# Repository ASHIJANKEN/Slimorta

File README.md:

# Slimorta
A slim and portable keyboad.

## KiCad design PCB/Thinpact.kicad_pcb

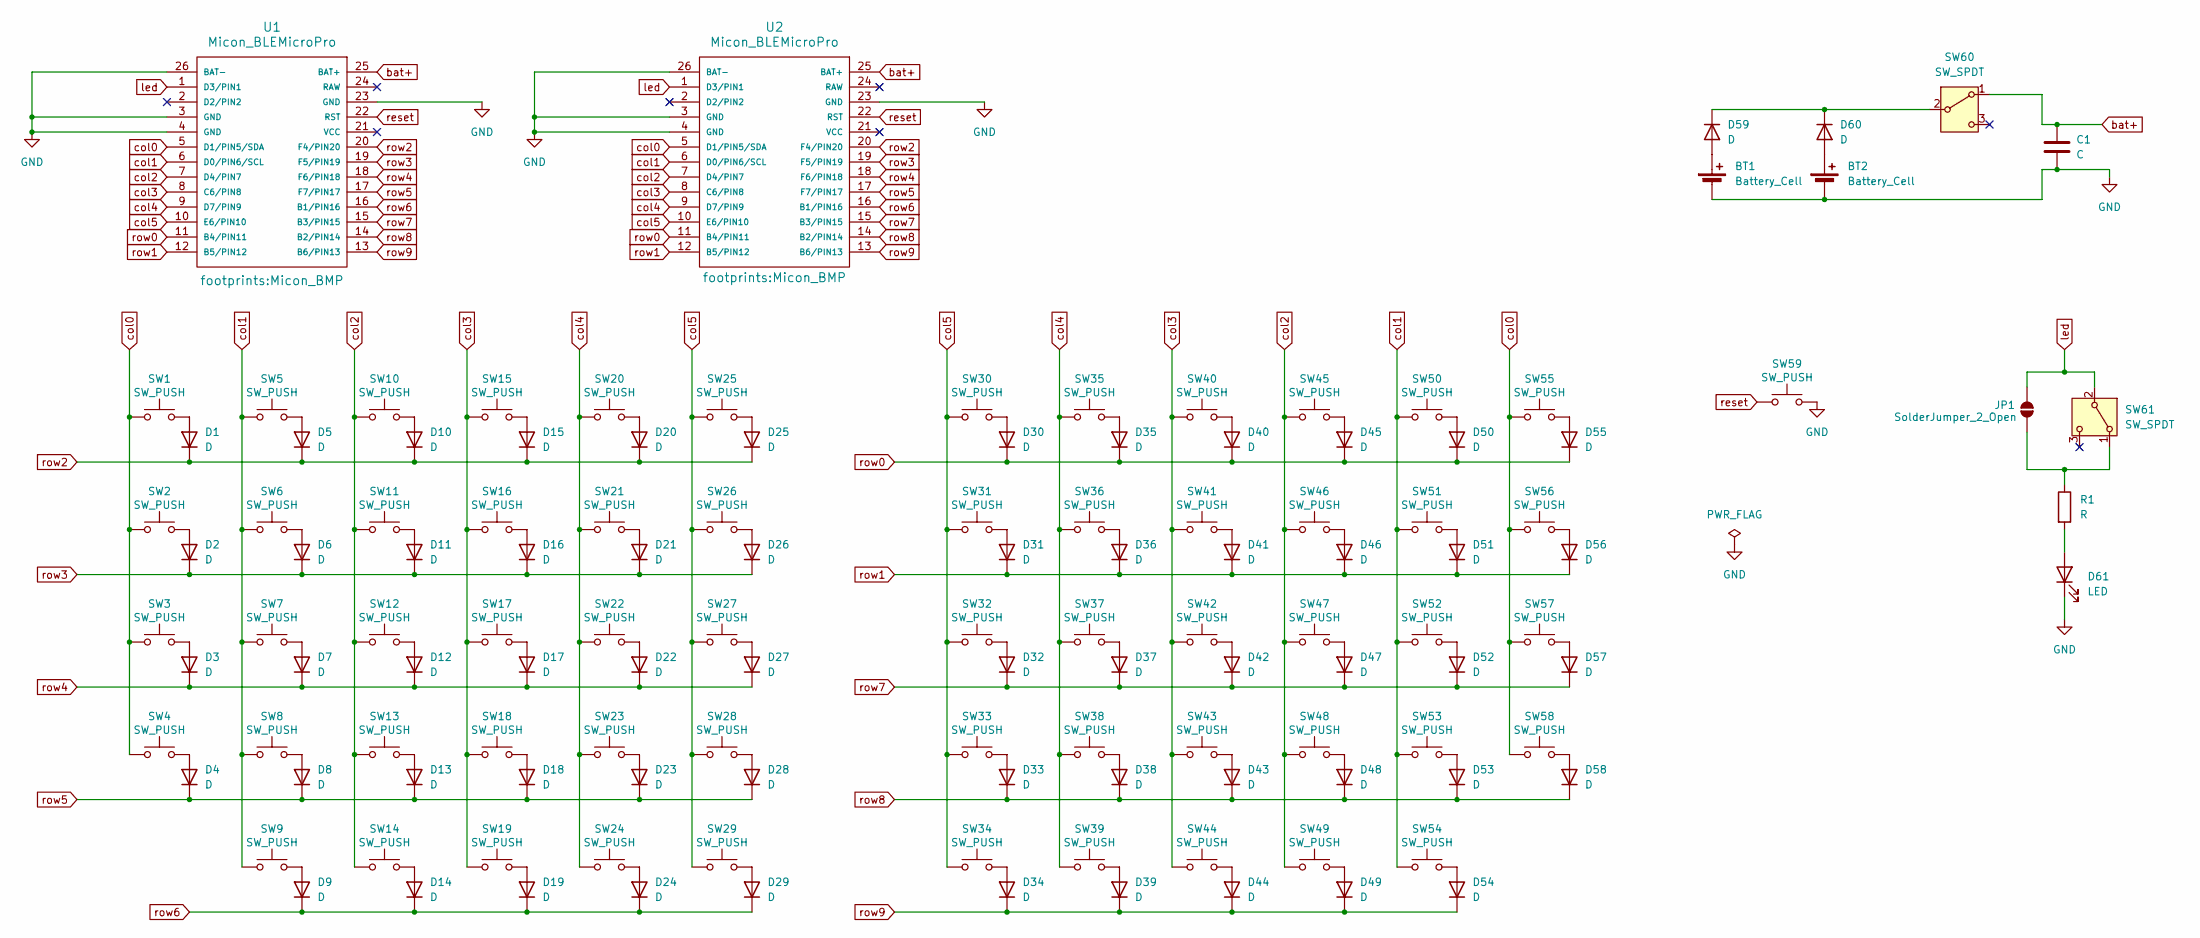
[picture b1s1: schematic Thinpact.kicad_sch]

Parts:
BT1, BT2: Battery_Cell; HU1632
C1: C; C_1206_3216Metric_Pad1.33x1.80mm_HandSolder
D1, D2, D3, D4, D5, D6, D7, D8, D9, D10, D11, D12, D13, D14, D15, D16, D17, D18, D19, D20, D21, D22, D23, D24, D25, D26, D27, D28, D29, D30, D31, D32, D33, D34, D35, D36, D37, D38, D39, D40, D41, D42, D43, D44, D45, D46, D47, D48, D49, D50, D51, D52, D53, D54, D55, D56, D57, D58, D59, D60: D; Diode_SMD
D61: LED; LED_D3.0mm
JP1: SolderJumper_2_Open; SolderJumper-2_P1.3mm_Bridged_RoundedPad1.0x1.5mm
R1: R; R_Axial_DIN0204_L3.6mm_D1.6mm_P1.90mm_Vertical
SW1, SW2, SW3, SW4: SW_PUSH; Choc_Hotswap_1u_Small
SW5, SW6, SW7, SW8, SW9, SW10, SW11, SW12, SW13, SW14, SW15, SW16, SW17, SW18, SW19, SW20, SW21, SW22, SW23, SW25, SW26, SW27, SW28, SW30, SW31, SW32, SW33, SW35, SW36, SW37, SW38, SW40, SW41, SW42, SW43, SW44, SW45, SW46, SW47, SW48, SW49, SW50, SW51, SW52, SW53, SW54, SW55, SW56, SW57, SW58: SW_PUSH; Choc_Hotswap_1u
SW24, SW29, SW34, SW39: SW_PUSH; Choc_Hotswap_1.25u
SW59: SW_PUSH; ResetSW
SW60: SW_SPDT; SK-12D11VG3
SW61: SW_SPDT; SS-12D00G3
U1, U2: Micon_BLEMicroPro; Micon_BMP

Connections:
GND: BT1.2 (-), BT2.2 (-), C1.2, D61.1 (K), SW59.2, U1.3 (GND), U1.4 (GND), U1.23 (GND), U1.26 (BAT-), U2.3 (GND), U2.4 (GND), U2.23 (GND), U2.26 (BAT-)
unnamed: BT1.1 (+), D59.2 (A)
unnamed: BT2.1 (+), D60.2 (A)
unnamed: D1.2 (A), SW1.2
unnamed: D2.2 (A), SW2.2
unnamed: D3.2 (A), SW3.2
unnamed: D4.2 (A), SW4.2
unnamed: D5.2 (A), SW5.2
unnamed: D6.2 (A), SW6.2
unnamed: D7.2 (A), SW7.2
unnamed: D8.2 (A), SW8.2
unnamed: D9.2 (A), SW9.2
unnamed: D10.2 (A), SW10.2
unnamed: D11.2 (A), SW11.2
unnamed: D12.2 (A), SW12.2
unnamed: D13.2 (A), SW13.2
unnamed: D14.2 (A), SW14.2
unnamed: D15.2 (A), SW15.2
unnamed: D16.2 (A), SW16.2
unnamed: D17.2 (A), SW17.2
unnamed: D18.2 (A), SW18.2
unnamed: D19.2 (A), SW19.2
unnamed: D20.2 (A), SW20.2
unnamed: D21.2 (A), SW21.2
unnamed: D22.2 (A), SW22.2
unnamed: D23.2 (A), SW23.2
unnamed: D24.2 (A), SW24.2
unnamed: D25.2 (A), SW25.2
unnamed: D26.2 (A), SW26.2
unnamed: D27.2 (A), SW27.2
unnamed: D28.2 (A), SW28.2
unnamed: D29.2 (A), SW29.2
unnamed: D30.2 (A), SW30.2
unnamed: D31.2 (A), SW31.2
unnamed: D32.2 (A), SW32.2
unnamed: D33.2 (A), SW33.2
unnamed: D34.2 (A), SW34.2
unnamed: D35.2 (A), SW35.2
unnamed: D36.2 (A), SW36.2
unnamed: D37.2 (A), SW37.2
unnamed: D38.2 (A), SW38.2
unnamed: D39.2 (A), SW39.2
unnamed: D40.2 (A), SW40.2
unnamed: D41.2 (A), SW41.2
unnamed: D42.2 (A), SW42.2
unnamed: D43.2 (A), SW43.2
unnamed: D44.2 (A), SW44.2
unnamed: D45.2 (A), SW45.2
unnamed: D46.2 (A), SW46.2
unnamed: D47.2 (A), SW47.2
unnamed: D48.2 (A), SW48.2
unnamed: D49.2 (A), SW49.2
unnamed: D50.2 (A), SW50.2
unnamed: D51.2 (A), SW51.2
unnamed: D52.2 (A), SW52.2
unnamed: D53.2 (A), SW53.2
unnamed: D54.2 (A), SW54.2
unnamed: D55.2 (A), SW55.2
unnamed: D56.2 (A), SW56.2
unnamed: D57.2 (A), SW57.2
unnamed: D58.2 (A), SW58.2
unnamed: D59.1 (K), D60.1 (K), SW60.2 (B)
unnamed: D61.2 (A), R1.2
unnamed: JP1.1 (A), R1.1, SW61.1 (A)
bat+: C1.1, SW60.1 (A), U1.25 (BAT+), U2.25 (BAT+)
col0: SW1.1, SW2.1, SW3.1, SW4.1, SW55.1, SW56.1, SW57.1, SW58.1, U1.5 (D1/PIN5/SDA), U2.5 (D1/PIN5/SDA)
col1: SW5.1, SW6.1, SW7.1, SW8.1, SW9.1, SW50.1, SW51.1, SW52.1, SW53.1, SW54.1, U1.6 (D0/PIN6/SCL), U2.6 (D0/PIN6/SCL)
col2: SW10.1, SW11.1, SW12.1, SW13.1, SW14.1, SW45.1, SW46.1, SW47.1, SW48.1, SW49.1, U1.7 (D4/PIN7), U2.7 (D4/PIN7)
col3: SW15.1, SW16.1, SW17.1, SW18.1, SW19.1, SW40.1, SW41.1, SW42.1, SW43.1, SW44.1, U1.8 (C6/PIN8), U2.8 (C6/PIN8)
col4: SW20.1, SW21.1, SW22.1, SW23.1, SW24.1, SW35.1, SW36.1, SW37.1, SW38.1, SW39.1, U1.9 (D7/PIN9), U2.9 (D7/PIN9)
col5: SW25.1, SW26.1, SW27.1, SW28.1, SW29.1, SW30.1, SW31.1, SW32.1, SW33.1, SW34.1, U1.10 (E6/PIN10), U2.10 (E6/PIN10)
led: JP1.2 (B), SW61.2 (B), U1.1 (D3/PIN1), U2.1 (D3/PIN1)
reset: SW59.1, U1.22 (RST), U2.22 (RST)
row0: D30.1 (K), D35.1 (K), D40.1 (K), D45.1 (K), D50.1 (K), D55.1 (K), U1.11 (B4/PIN11), U2.11 (B4/PIN11)
row1: D31.1 (K), D36.1 (K), D41.1 (K), D46.1 (K), D51.1 (K), D56.1 (K), U1.12 (B5/PIN12), U2.12 (B5/PIN12)
row2: D1.1 (K), D5.1 (K), D10.1 (K), D15.1 (K), D20.1 (K), D25.1 (K), U1.20 (F4/PIN20), U2.20 (F4/PIN20)
row3: D2.1 (K), D6.1 (K), D11.1 (K), D16.1 (K), D21.1 (K), D26.1 (K), U1.19 (F5/PIN19), U2.19 (F5/PIN19)
row4: D3.1 (K), D7.1 (K), D12.1 (K), D17.1 (K), D22.1 (K), D27.1 (K), U1.18 (F6/PIN18), U2.18 (F6/PIN18)
row5: D4.1 (K), D8.1 (K), D13.1 (K), D18.1 (K), D23.1 (K), D28.1 (K), U1.17 (F7/PIN17), U2.17 (F7/PIN17)
row6: D9.1 (K), D14.1 (K), D19.1 (K), D24.1 (K), D29.1 (K), U1.16 (B1/PIN16), U2.16 (B1/PIN16)
row7: D32.1 (K), D37.1 (K), D42.1 (K), D47.1 (K), D52.1 (K), D57.1 (K), U1.15 (B3/PIN15), U2.15 (B3/PIN15)
row8: D33.1 (K), D38.1 (K), D43.1 (K), D48.1 (K), D53.1 (K), D58.1 (K), U1.14 (B2/PIN14), U2.14 (B2/PIN14)
row9: D34.1 (K), D39.1 (K), D44.1 (K), D49.1 (K), D54.1 (K), U1.13 (B6/PIN13), U2.13 (B6/PIN13)

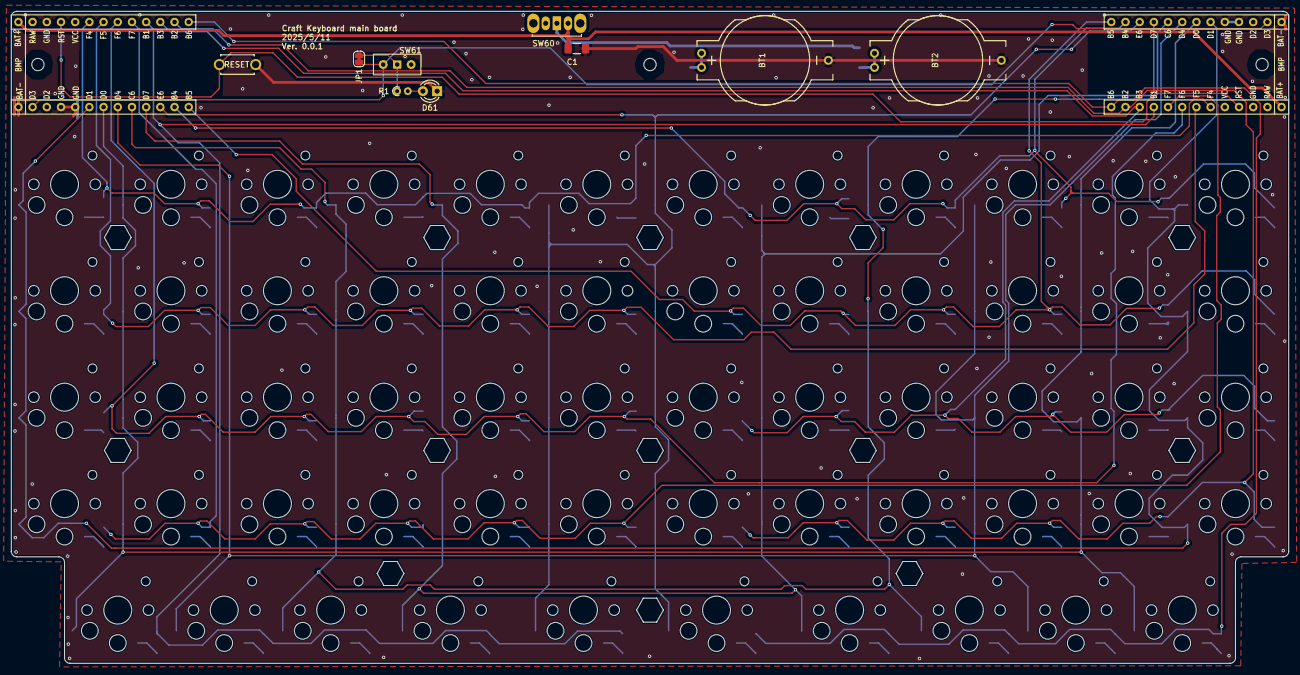
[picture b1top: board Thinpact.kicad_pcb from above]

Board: 2 copper layers, 228.5 x 116.6 mm, 145 parts (1 on the bottom side), 83 nets.

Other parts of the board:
H1, H2, H3: H; m2_Screw_Hole
H4, H5, H6, H7, H8, H9, H10, H11, H12, H13, H14, H15, H16: H; m2_Spacer_Hole_hex

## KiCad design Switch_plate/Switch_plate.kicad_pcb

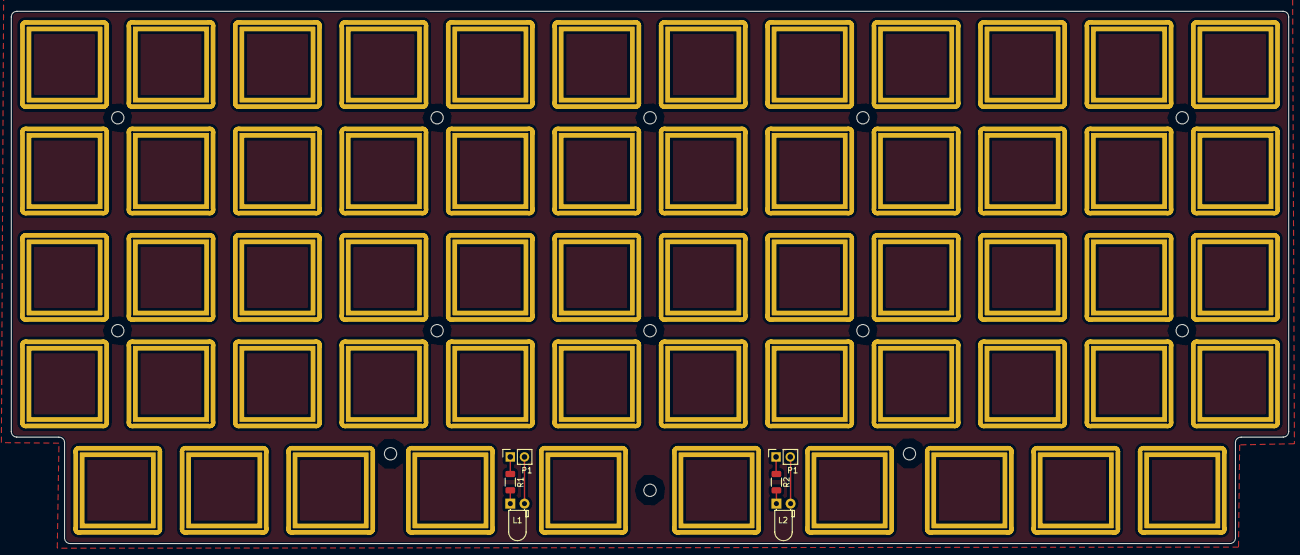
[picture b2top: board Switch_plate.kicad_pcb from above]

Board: 2 copper layers, 228.6 x 95.2 mm, 77 parts (0 on the bottom side), 6 nets.

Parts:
L1, L2: LED_D3.0mm_Horizontal_O1.27mm_Z2.0mm
P1, P1#2: PinSocket_1x02_P2.54mm_Vertical
R1, R2: R_1206_3216Metric
Ref**: Val**; m2_Screw_Hole
Ref**#2, Ref**#3, Ref**#4, Ref**#5, Ref**#6, Ref**#7, Ref**#8, Ref**#9, Ref**#10, Ref**#11, Ref**#12, Ref**#13: Val**; m2_Screw_Hole
SW1, SW2, SW3, SW4, SW5, SW6, SW7, SW8, SW9, SW10, SW11, SW12, SW13, SW14, SW15, SW16, SW17, SW18, SW19, SW20, SW21, SW22, SW23, SW25, SW26, SW27, SW28, SW30, SW31, SW32, SW33, SW35, SW36, SW37, SW38, SW40, SW41, SW42, SW43, SW44, SW45, SW46, SW47, SW48, SW49, SW50, SW51, SW52, SW53, SW54, SW55, SW56, SW57, SW58: SW_PUSH; SW_Hole_TH_1u
SW24, SW29, SW34, SW39: SW_PUSH; SW_Hole_TH_1.25u

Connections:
col0: SW1.1, SW2.1, SW3.1, SW4.1, SW55.1, SW56.1, SW57.1, SW58.1
col1: SW5.1, SW6.1, SW7.1, SW8.1, SW9.1, SW50.1, SW51.1, SW52.1, SW53.1, SW54.1
col2: SW10.1, SW11.1, SW12.1, SW13.1, SW14.1, SW45.1, SW46.1, SW47.1, SW48.1, SW49.1
col3: SW15.1, SW16.1, SW17.1, SW18.1, SW19.1, SW40.1, SW41.1, SW42.1, SW43.1, SW44.1
col4: SW20.1, SW21.1, SW22.1, SW23.1, SW24.1, SW35.1, SW36.1, SW37.1, SW38.1, SW39.1
col5: SW25.1, SW26.1, SW27.1, SW28.1, SW29.1, SW30.1, SW31.1, SW32.1, SW33.1, SW34.1

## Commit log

2025-05-04 Update initial commit
2025-05-04 Add .gitignore
2025-05-04 Add KLE json file
2025-05-06 Add Kicad files
2025-05-10 Update sch and kicad_pcb(not routed)
2025-05-10 Update sch and kicad_pcb
2025-05-10 Add Switch_plate
2025-05-11 Circuit patterns for v0.0.1
2025-05-18 Add gerber data for v0.0.1
2025-05-26 Add case v0.0.1
2025-05-31 Add kle data for making ble configuration
2025-06-01 Change project name and directory structure
